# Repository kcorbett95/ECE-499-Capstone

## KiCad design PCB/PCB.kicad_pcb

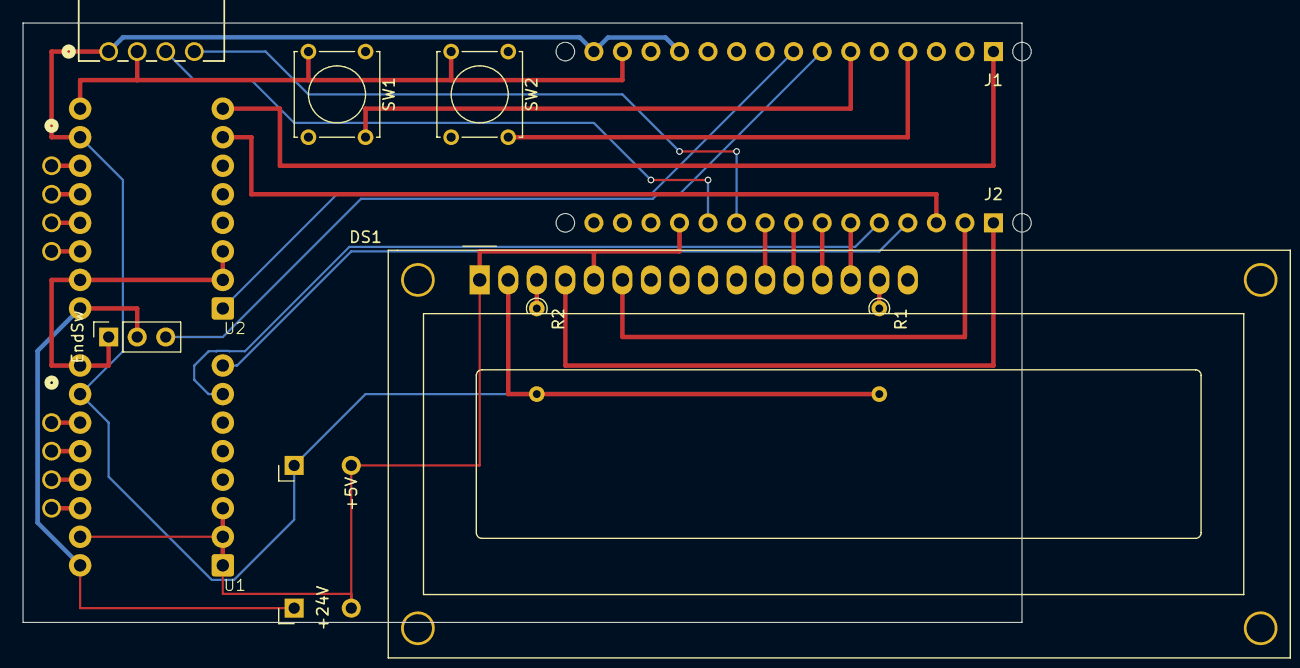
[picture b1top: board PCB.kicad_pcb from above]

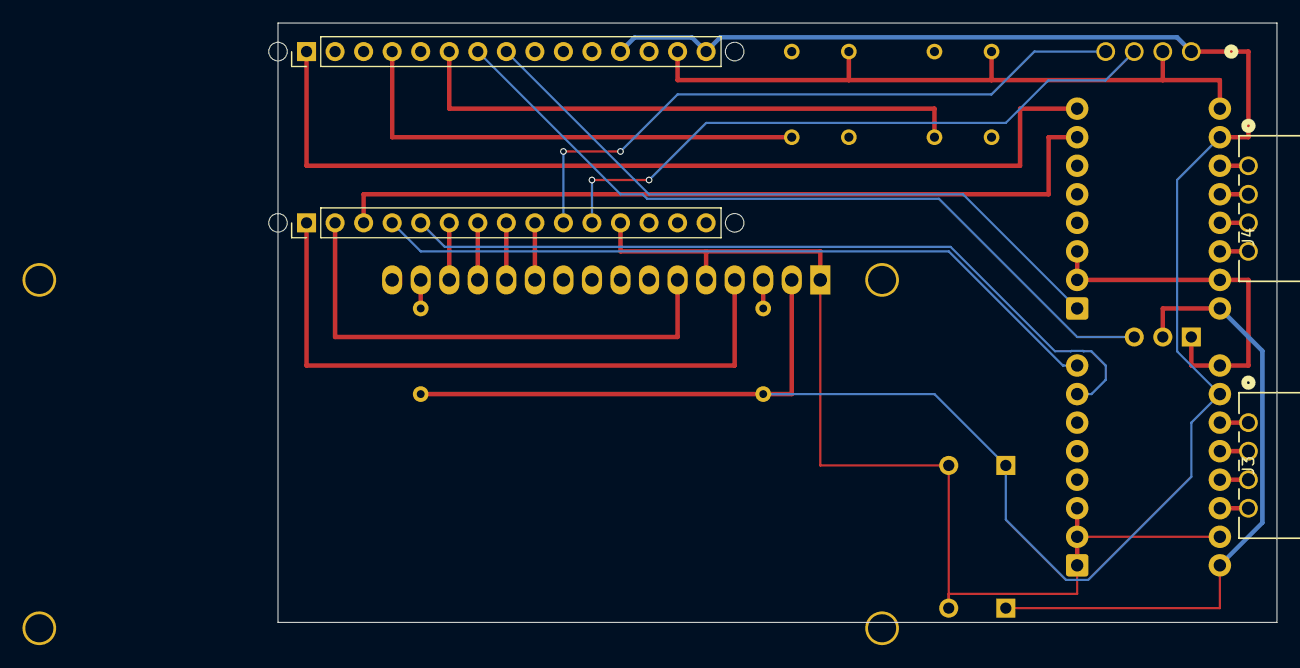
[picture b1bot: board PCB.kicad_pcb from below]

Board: 2 copper layers, 88.9 x 53.3 mm, 19 parts (4 on the bottom side), 30 nets.

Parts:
+5V, +24V: PinHeader_1x02_P2.54mm_Vertical
DS1: HY1602E; WC1602A
EndSw: PinSocket_1x03_P2.54mm_Vertical
J1: Analog; PinHeader_1x15_P2.54mm_Vertical
J2: Digital; PinHeader_1x15_P2.54mm_Vertical
J3, J4, J5: Conn_01x04_Pin; CONN_70553-xxxx_04_MOL
MH1, MH2, MH3, MH4: MountingHole_65mil
R1: 220; R_Axial_DIN0204_L3.6mm_D1.6mm_P1.90mm_Vertical
R2: 1k2; R_Axial_DIN0204_L3.6mm_D1.6mm_P1.90mm_Vertical
SW1, SW2: SW_DPST; SW_Tactile_Straight_KSL0Axx1LFTR
U1, U2: BTT-TMC2209

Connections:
+5V: +5V.1, DS1.2 (VDD), J1.12, J1.15, J5.1, R1.2, R2.2, U1.10 (VDD), U2.10 (VDD)
+24V: +24V.1, EndSw.2, U1.16 (VM), U2.16 (VM)
/*D3: J2.10, J5.4
/*D5: DS1.12 (D5), J2.8
/*D6: DS1.13 (D6), J2.7
/*D9: J2.4, U1.8 (DIR)
/*D10/SS: J2.3, U2.7 (STEP)
/*D11/MOSI: DS1.6 (E), J2.2
/A0: J1.4, SW2.1
/A2: J1.6, SW1.1
/A3: EndSw.3, J1.7
/A4/SDA: J1.8, U2.1 (EN)
/D2: J2.11, J5.3
/D4: DS1.11 (D4), J2.9
/D7: DS1.14 (D7), J2.6
/D8: J2.5, U1.7 (STEP)
/D12/MISO: DS1.4 (RS), J2.1
/D13/SCK: J1.1, U2.8 (DIR)
/~RESET: J1.13, J2.13
GND: +5V.2, +24V.2, DS1.1 (VSS), DS1.5 (R/W), DS1.16 (LED(-)), EndSw.1, J1.14, J2.12, J5.2, SW1.2, SW2.2, U1.1 (EN), U1.2 (MS1), U1.3 (MS2), U1.9 (GND), U1.15 (GND), U2.2 (MS1), U2.3 (MS2), U2.9 (GND), U2.15 (GND)
unnamed: DS1.15 (LED(+)), R1.1
unnamed: DS1.3 (VO), R2.1
unnamed: J3.1, U1.11 (B2)
unnamed: J3.2, U1.12 (B1)
unnamed: J3.3, U1.13 (A1)
unnamed: J3.4, U1.14 (A2)
unnamed: J4.1, U2.11 (B2)
unnamed: J4.2, U2.12 (B1)
unnamed: J4.3, U2.13 (A1)
unnamed: J4.4, U2.14 (A2)

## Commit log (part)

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2026-06-07 Initial Commit
    Created README.md file
2026-06-07 PlatformIO Init
    Created PlatformIO programming environment
2026-06-21 Encoder 1.0
    Encoder working with simple counter and revolution increment/decrement. Will improve functionality and tweak areas at a later point.
2026-06-21 Cleanup
    Cleaned up the encoder section a touch
2026-06-21 Misc Json Updates
2026-06-21 LCD init and working, with wiring
2026-06-21 Initial Stepper-Linear
    Initial Stepper_Linaer push. Added library and created class for stepper motor
2026-06-21 untracked files on main: 312874b Merge branch 'Encoder'
2026-06-21 index on main: 312874b Merge branch 'Encoder'
2026-06-22 Encoder printing to LCD, Working
2026-06-22 LCD wiring table update
2026-06-22 Linear Actuator to Encoder function
2026-06-22 Cleanup of functions
2026-06-22 Working Linear Drive on Encoder Reference
2026-06-22 Cleaned up encoder related files
2026-06-22 Cleanup post merge
2026-06-24 Added Nano Pin Connection Table, DIR pin set to output
2026-06-26 Adjusted pinout and changed board type
2026-06-26 Misc
2026-06-26 included LCD
2026-06-26 WIP - There and back feature
2026-06-26 Homing switch working
2026-06-26 index on Stepper-Linear: 97ed83d Merge branch 'Stepper-Linear' of https://github.com/kcorbett95/ECE-499-Capstone into Stepper-Linear
2026-06-26 back-and-forth was working, but then fried stepper drivers. no idea why
2026-06-26 Working windings, needs tuning
